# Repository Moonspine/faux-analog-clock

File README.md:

# Faux Analog Clock

An analog clock composed entirely of LEDs

The build should be fairly self-explanatory. A KiCad 6 schematic and board layout are included in `Board\`  
Additionally, `Board\Faux Analog Clock Gerber.zip` is a ready-to-go Gerber plot of the board which can be sent directly to the PCB manufacturer of your choice.  
LED resistor values are mere suggestions, and you should experiment on a breadboard to see what works well with your chosen LEDs.  

The following photos show the clock operating with its "Fill 2" (F2) display mode active:  

# Debugging the build

In order to facilitate easier debugging during the build process, two LED tests are easily accessible on startup.  

If you press and hold "Select" as you turn the clock on, it will boot in "LED test 1" mode.  
This mode displays all LEDs at full brightness to help track down bad solder joints, backwards diodes, etc.  
This test mode is accessible via the utilities menu after startup. Press any key to resume the normal boot sequence.  

If you press and hold "Enter" as you turn the clock on, it will boot in "LED test 2" mode.  
This mode displays each LED in sequence. This is useful for tracking down solder bridges and confirming proper clock operation.  
This test mode is also accessible via the utilities menu after startup. Press any key to resume the normal boot sequence.  

# Using the menu

Press "Select" or "Enter" to enter the menu.  
Subsequent presses of "Select" will advance to different menu options.  
Pressing "Enter" will choose a menu option (either changing a setting or opening a submenu.)  
Pressing and holding "Select" for the amount of time defined by MENU_BACK_BUTTON_LONG_PRESS_MS will return to the previous menu (or close the menu if at the top menu.)  
If no buttons are pressed for MENU_TIMEOUT_MS milliseconds, the menu will close on its own.

## Main menu options
- tZ (72) = Timezone
- dS (d5) = Daylight Saving Time
- FE (FE) = Face effects (Clock face ring effects)
- Fd (Fd) = Fade effects
- br (br) = Brightness
- nb (nb) = Night brightness (multiplied by brightness)
- dY (d4) = Display mode
- Pd (Pd) = Pendulum period
- UT (U7) = Utilities

## Timezone menu

In this menu, you can select the timezone offset of the clock, in whole hour increments.  
These values are displayed in hexadecimal (sorry, 7-segment displays) ranging from "-C" (-12 hours) to "E" (+14 hours)

## Daylight Saving Time menu

In this menu, you can set whether DST is in effect ("Y") or not ("n")

## Face Effects menu

This menu controls the face edge lighting.
- "on" = Face effects are turned on (fading between inner and outer at sunrise/sunset)
- "ou" = Face effects are turned off, always light outer clock face ring
- "in" = Face effects are turned off, always light inner clock face ring
- "bo" = Face effects are turned off, always light both clock face rings

## Fade Effects menu

This menu turns the LED intensity fade effects on ("Y") or off ("n")

## Brightness menu

This menu controls overall clock LED brightness from 1 (dimmest) to 10 (brightest).

## Night Brightness menu

This menu controls overall clock LED brightness at night (from 6 PM to 6 AM) from 1 (dimmest) to 10 (brightest).  
This value is multiplied by the overall clock brightness, making it effectively a scalar for clock brightness that's only applied at night.

## Display mode menu

This menu allows you to select between different clock face display modes.
- "An" = Analog mode. This is the classic analog clock face, showing one LED for hours, one for minutes, and one for seconds.
- "bn" = Binary mode. This mode displays H/M/S in binary. The LSb is at 12 o'clock, and the bits are displayed in clockwise order from there. The hours use 3 LEDs per bit (displaying a 4-bit number in total), and the minutes and seconds each use 10 LEDs per bit (displaying a 6-bit number).
- "F1" = Fill mode 1. This mode fills the hour/minute/second rings as time progresses, clearing them at the turn of the minute/hour.
- "F2" = Fill mode 2. This mode fills the hour/minute/second rings on even minutes/hours/AM (respectively), and empties the rings on odd mintes/hours/PM.
- "In" = Inverted analog mode. This is the same as analog move, except that the LEDs are inverted.

## Pendulum period menu

This menu allows you to set the period of the pendulum.
- "FA" = Fast (1 second)
- "SL" = Slow (2 seconds)

## Utilities menu

This menu includes some useful utilities for testing your clock build.
- "RS" ("r5") = Reset the current time using the GPS
- "L1"        = Run LED test 1 (light all LEDs at max intensity) (press any button to end)
- "L2"        = Run LED test 2 (light LEDs at max intensity sequentially) (press any button to end)

# Customizing the clock

## Faux_Analog_Clock.ino

At the top of `Firmware/Faux_Analog_Clock/Faux_Analog_Clock.ino`, you can find many constants defined which alter the behavior of the clock.

You can change the fade animation rate by modifying variables in the "Animation timing variables" section.
- CLOCK_ANIM_*_FADE_TIME = The number of microseconds between each time the LEDs fade by 1 unit of intensity (255 is the max LED intensity)

Menu behavior can be configured as well:
- MENU_TIMEOUT_MS                = The number of milliseconds until the menu auto-closes after the last button press.
- MENU_BACK_BUTTON_LONG_PRESS_MS = The number of milliseconds the user must hold the "Select" button to return to the previous menu.

You can also change how often the GPS is used to set the RTC:
- TIMEKEEPER_GPS_TIME_SET_INTERVAL_SECONDS = Seconds in between time resets.

## ClockFace.h

FACE_INNER_HOURLY_BRIGHTNESS and FACE_OUTER_HOURLY_BRIGHTNESS define the brightness of the inner and outer edge rings on a per-hour basis.  
The first entry in each array is the brightness at midnight (hour 0), and the rest of the entries count up from there (1 AM, 2 AM, etc.)

## Pendulum.h
PENDULUM_LED_INDEX contains the LED indices of the pendulum for each individual millisecond following a second tick.  
The default pattern is a sinusoidal pendulum pattern that starts in the center and swings right then left.

## Timekeeper.h

In `Firmware/Faux_Analog_Clock/Timekeeper.h`, commenting out the following line will cause the timekeeper to use an internal millis()-based RTC rather than external RTC hardware:
```
#define USE_HARDWARE_RTC 1
```

You can also modify the amount of time that the timekeeper will attempt to get a fix before forcibly resetting the GPS (the default is 15 minutes):
```
#define GPS_RESET_TIMEOUT_MS 900000
```

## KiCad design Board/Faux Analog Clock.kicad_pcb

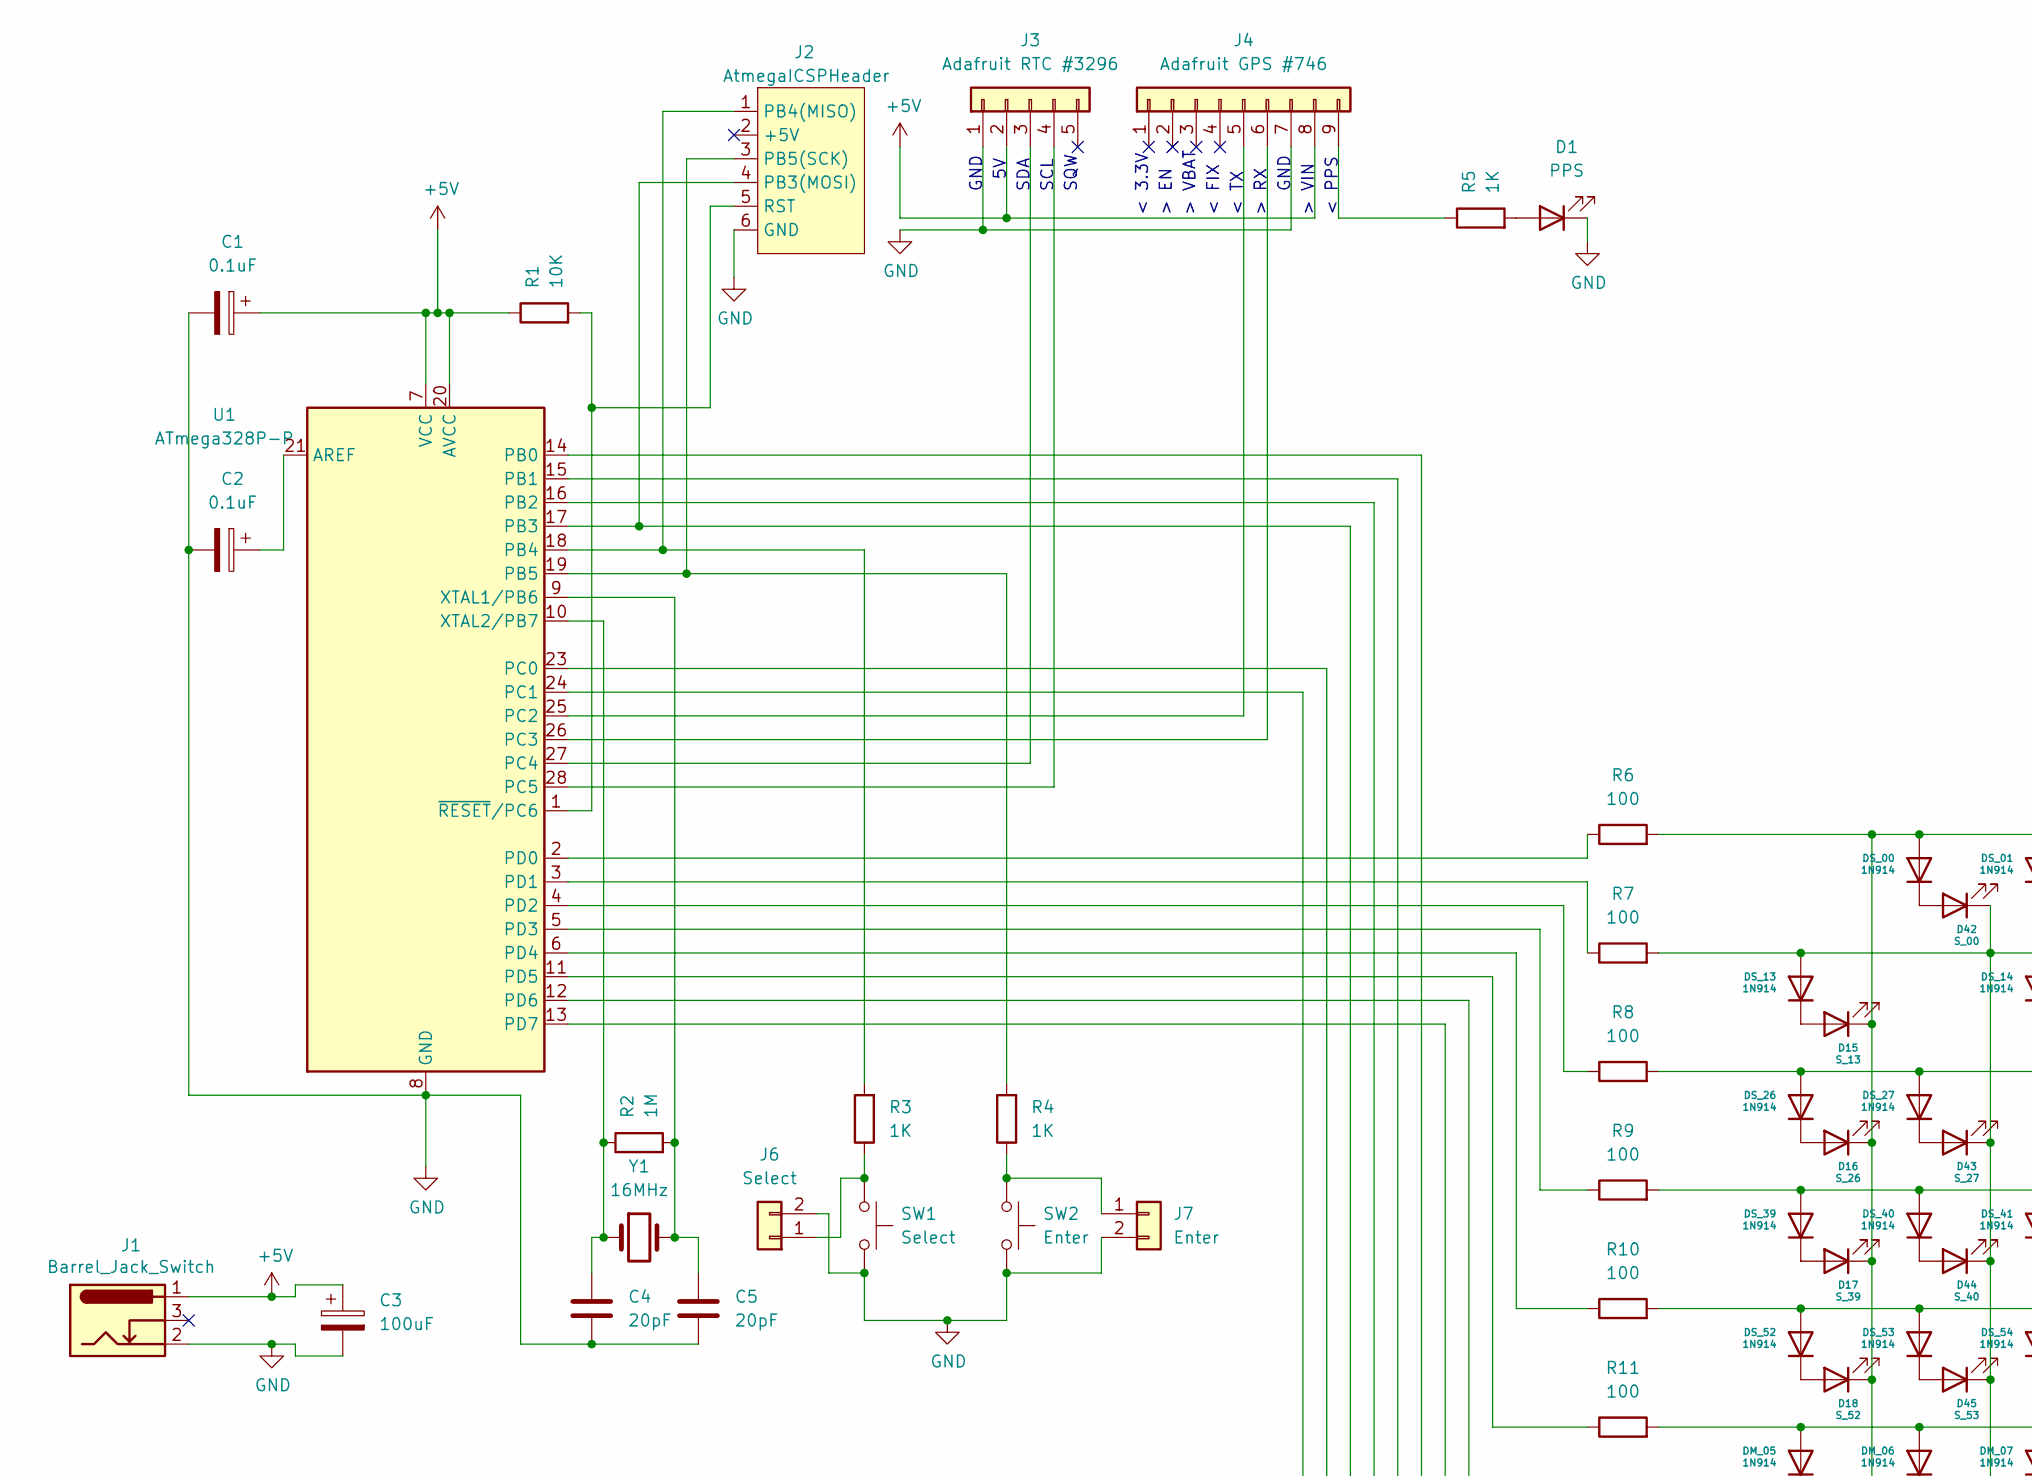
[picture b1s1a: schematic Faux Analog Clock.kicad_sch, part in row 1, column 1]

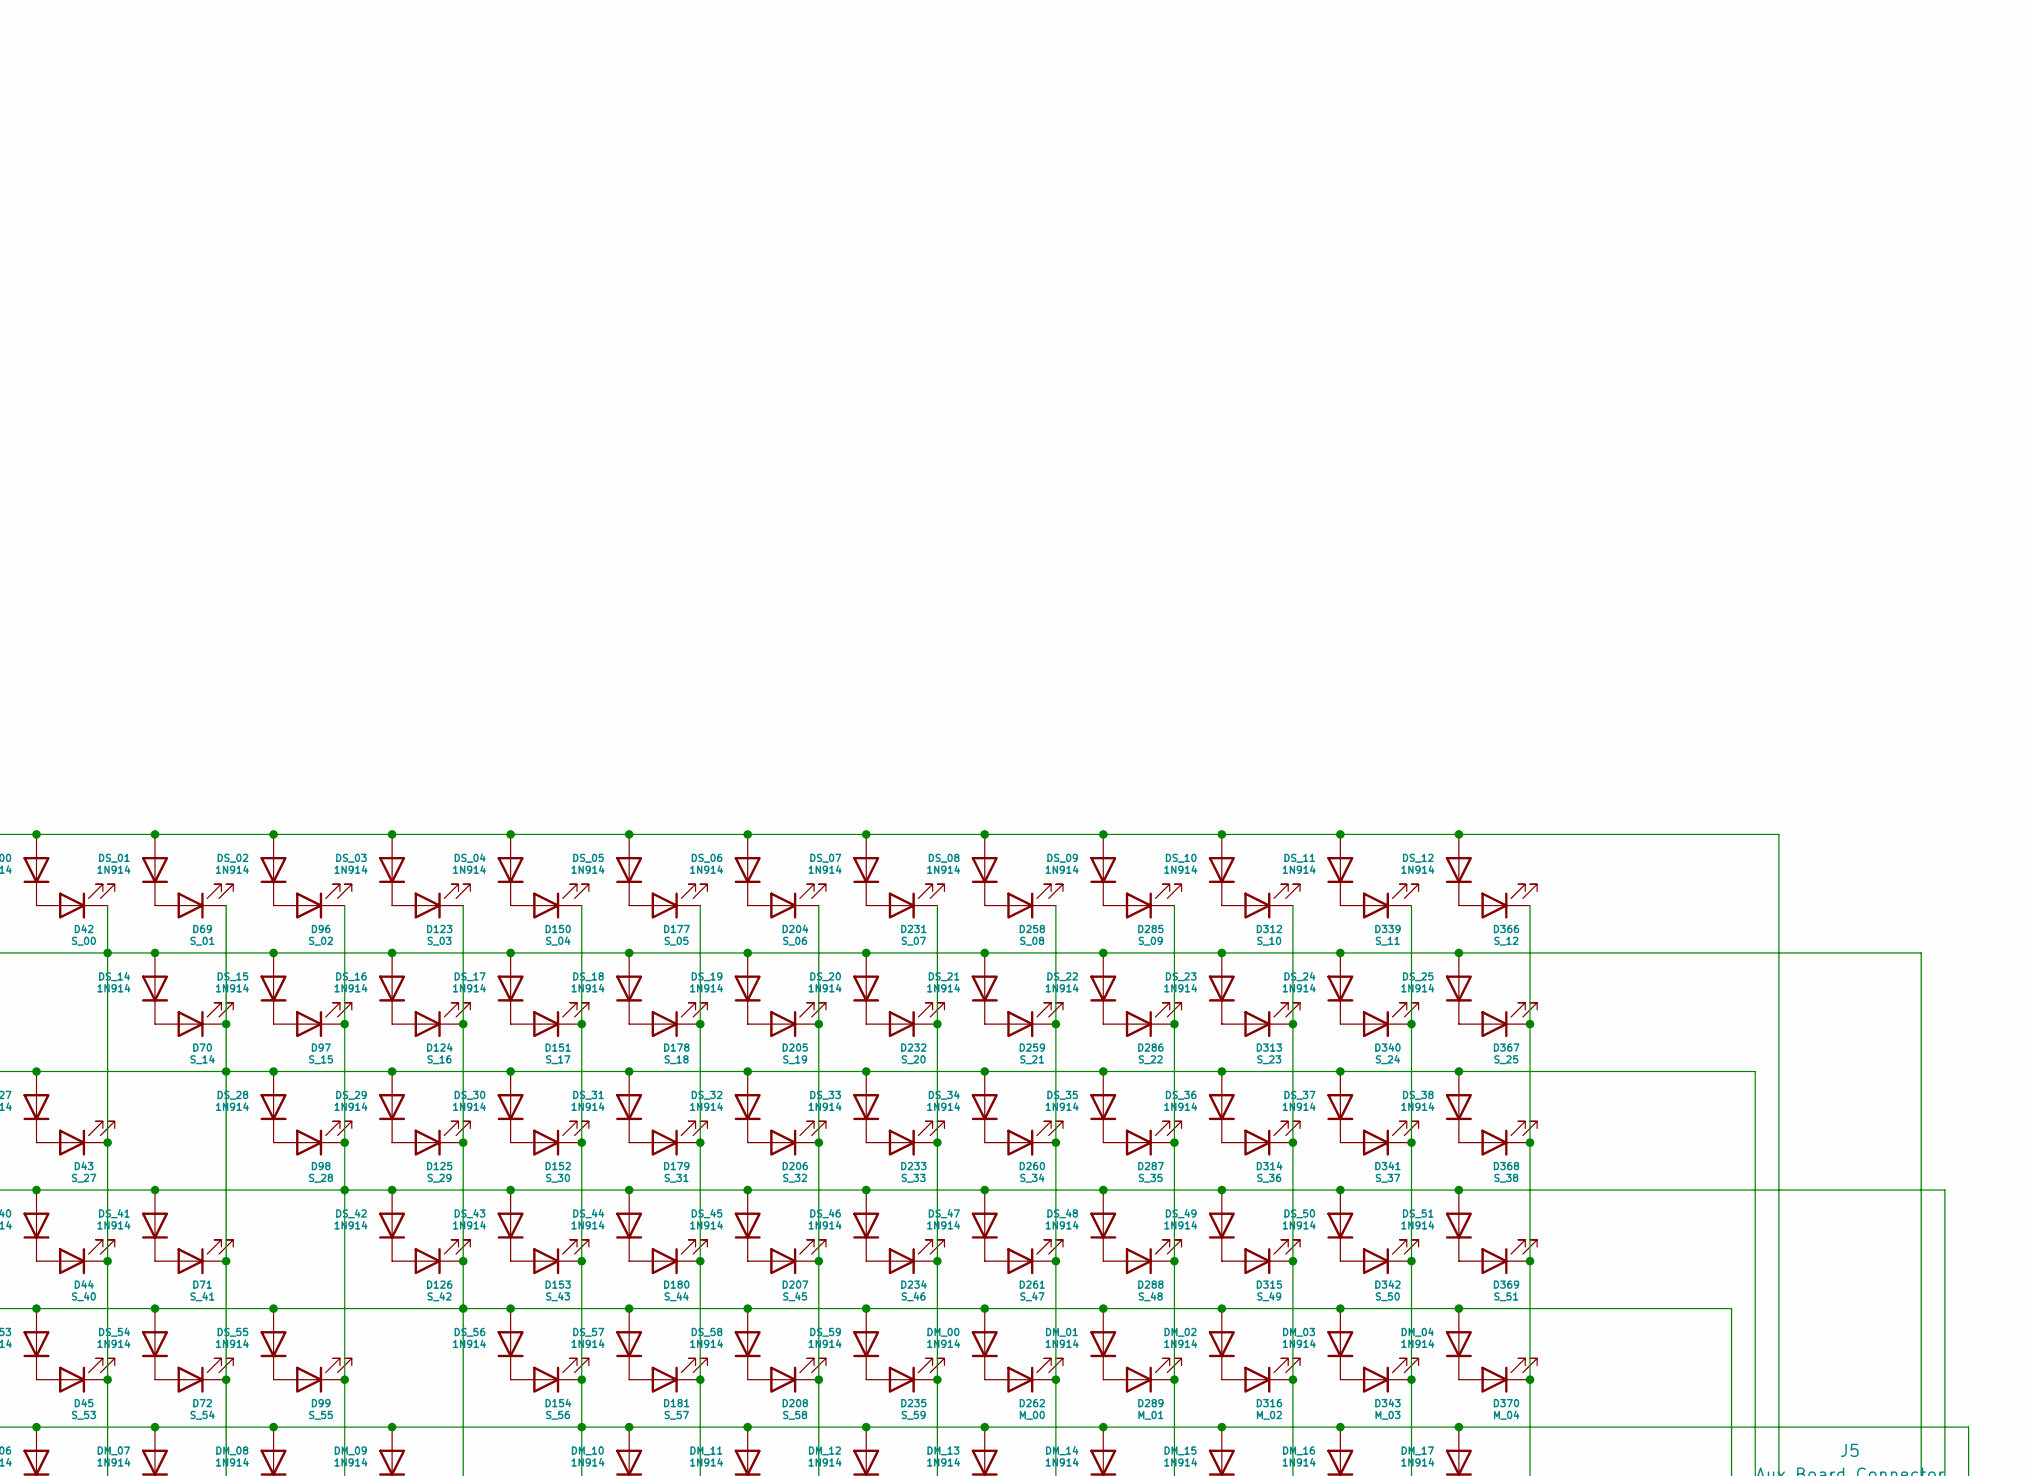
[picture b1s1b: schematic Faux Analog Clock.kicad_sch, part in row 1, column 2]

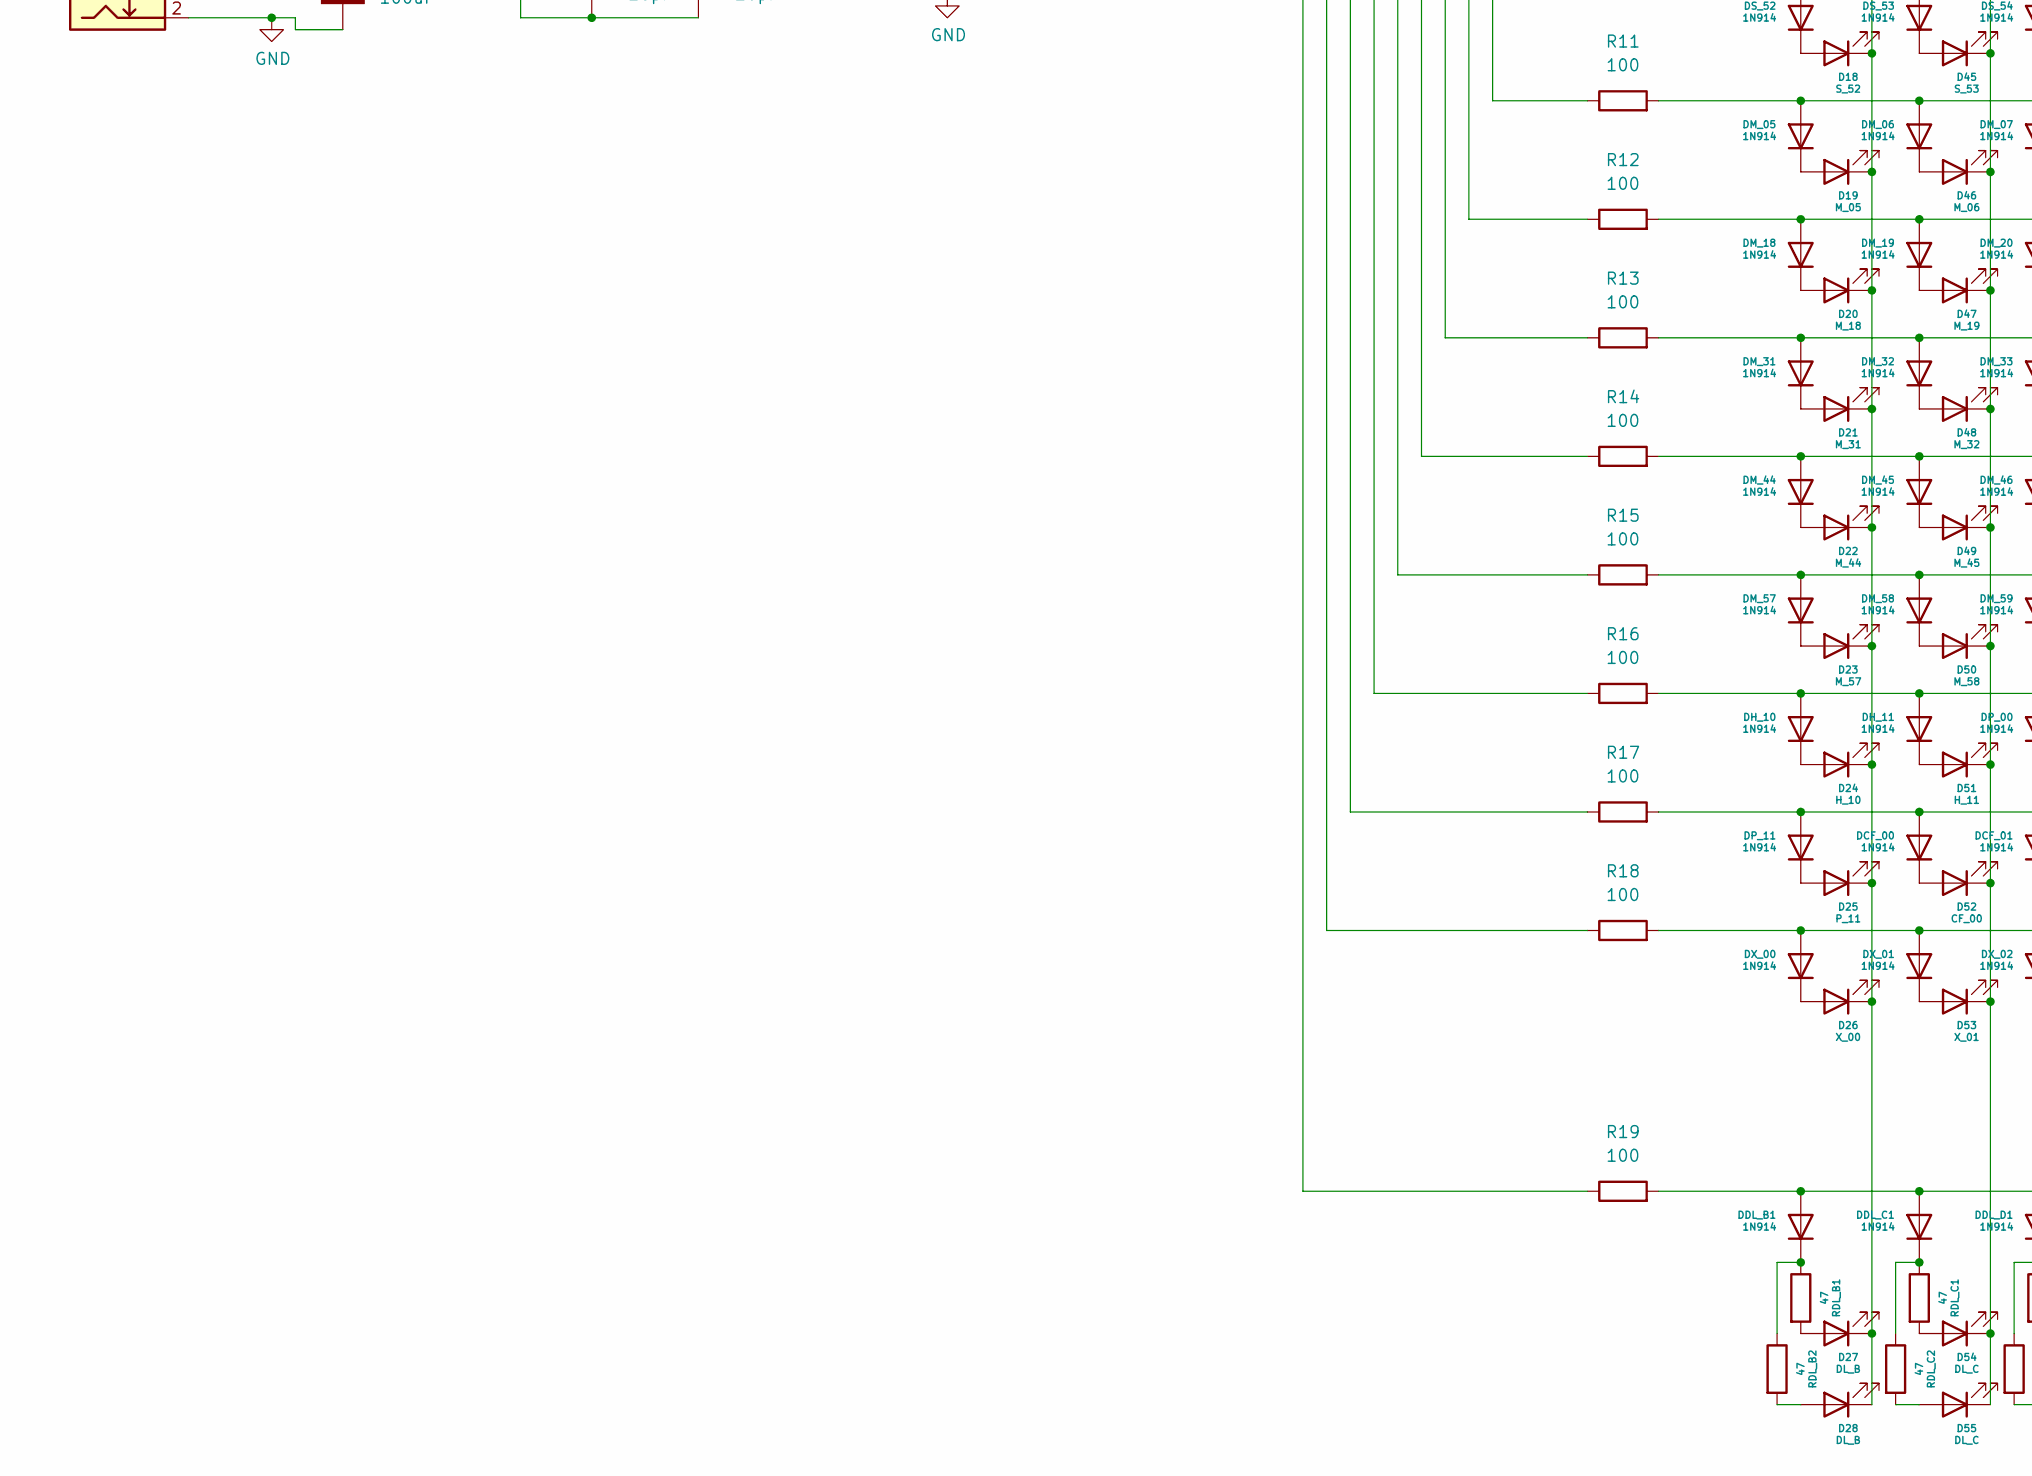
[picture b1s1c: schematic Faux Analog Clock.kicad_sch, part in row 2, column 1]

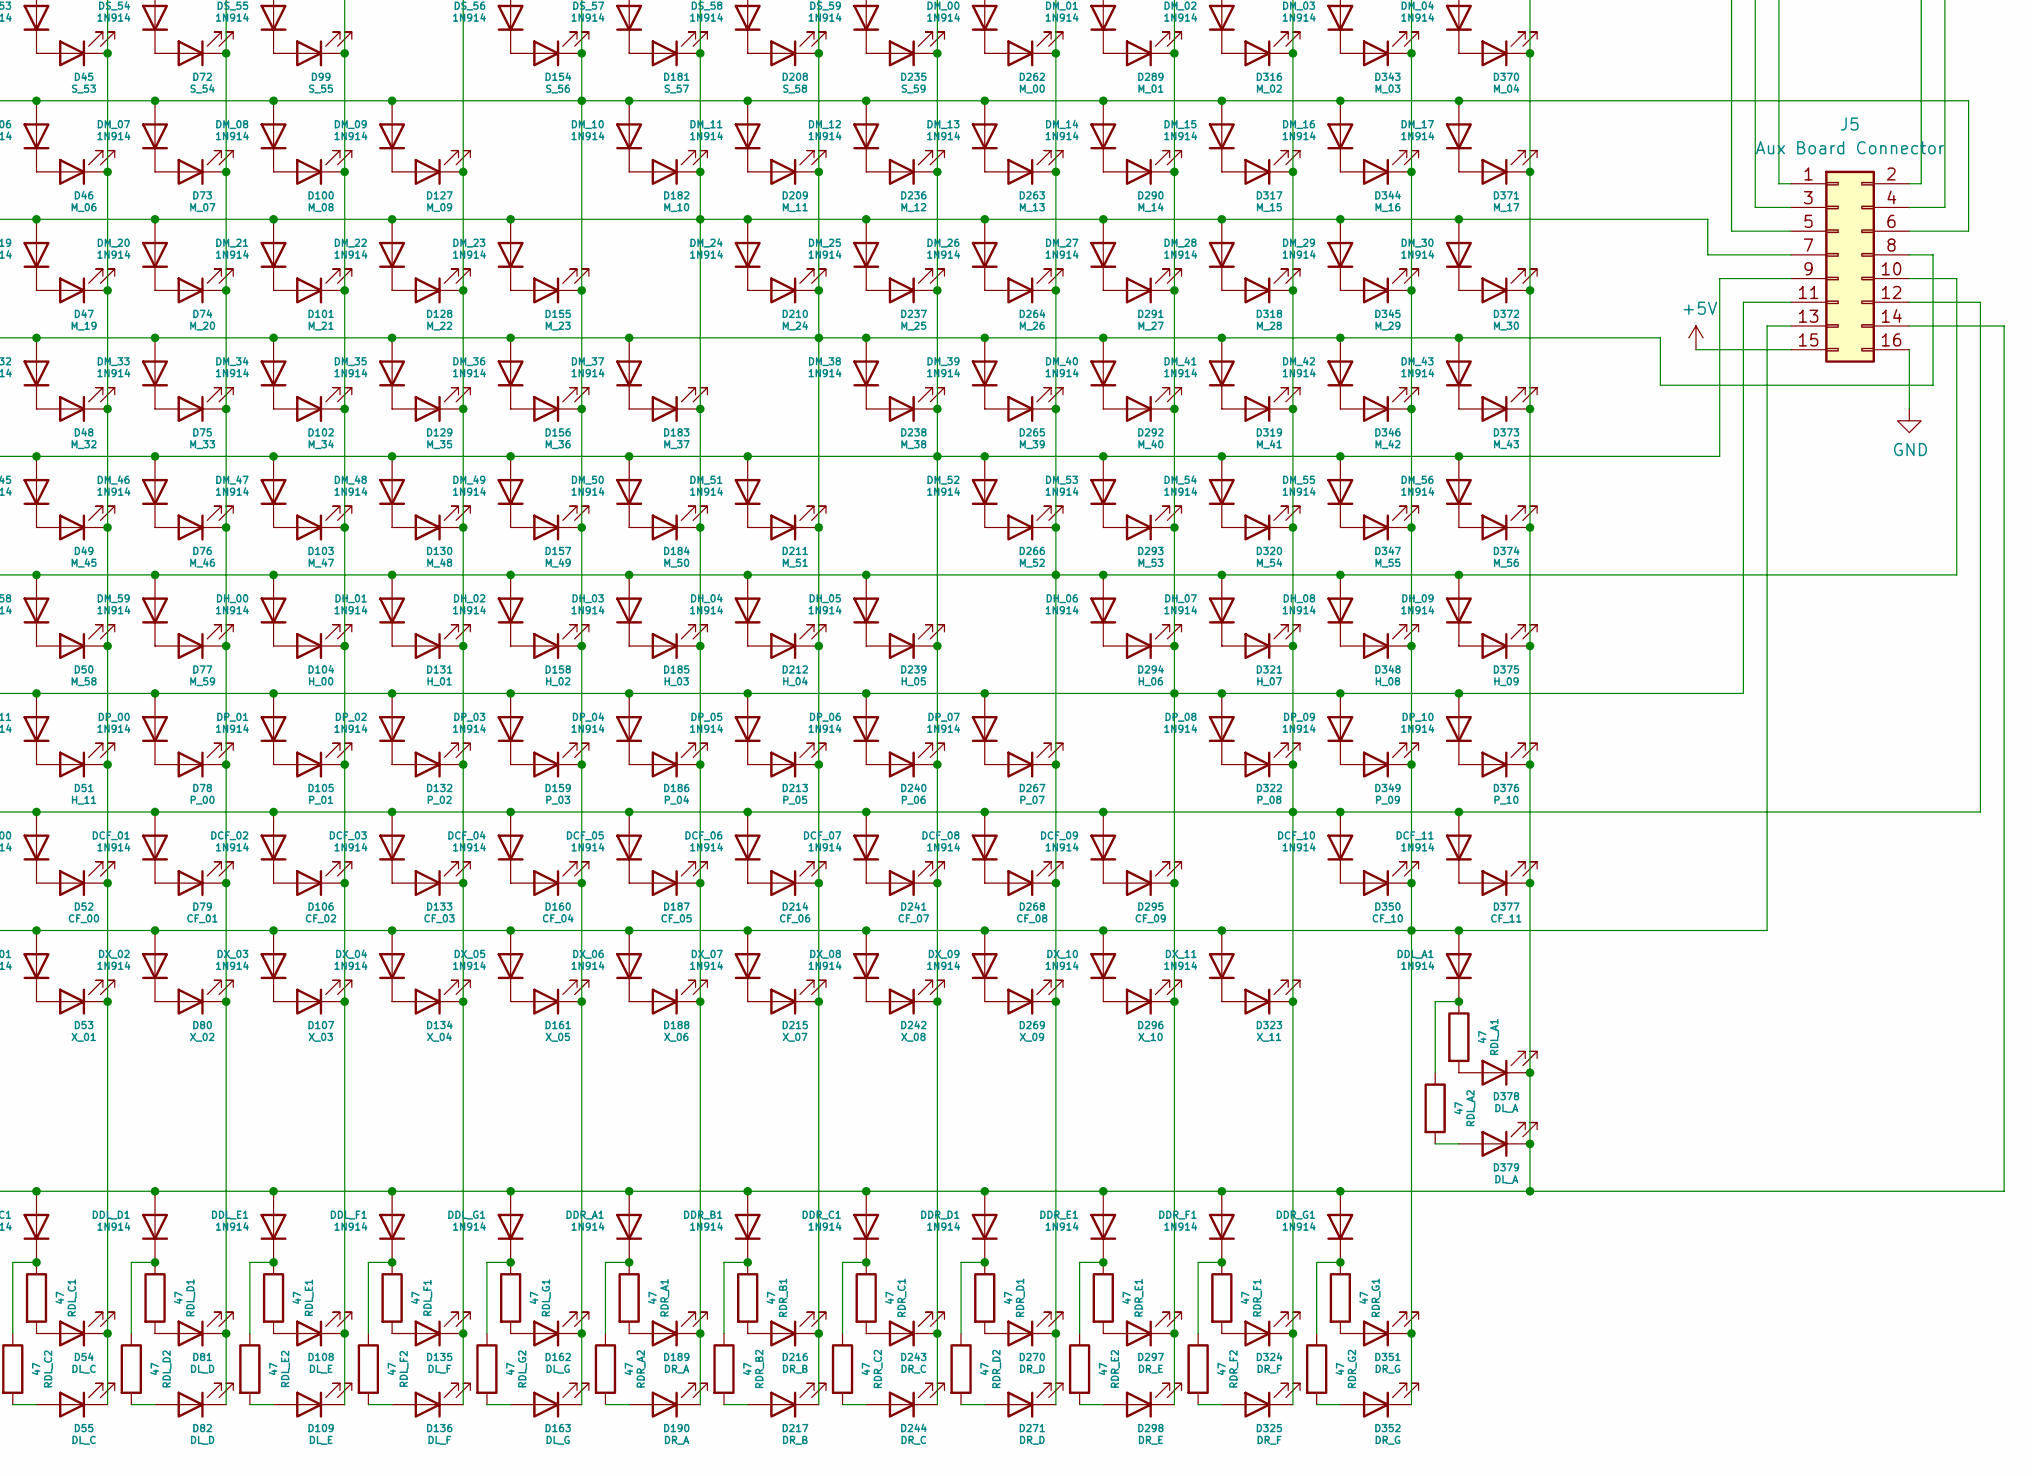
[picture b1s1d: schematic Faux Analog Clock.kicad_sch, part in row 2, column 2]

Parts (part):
C1, C2: 0.1uF; CP_Radial_Tantal_D5.0mm_P2.50mm
C3: 100uF; CP_Radial_D10.0mm_P3.50mm
C4, C5: 20pF; C_Disc_D5.0mm_W2.5mm_P2.50mm
D1: PPS; LED_D5.0mm
D15: S_13; LED_D5.0mm
D16: S_26; LED_D5.0mm
D17: S_39; LED_D5.0mm
D18: S_52; LED_D5.0mm
D19: M_05; LED_D5.0mm
D20: M_18; LED_D5.0mm
D21: M_31; LED_D5.0mm
D22: M_44; LED_D5.0mm
D23: M_57; LED_D5.0mm
D24: H_10; LED_D5.0mm
D25: P_11; LED_D5.0mm
D26: X_00; LED_D5.0mm
D27, D28: DL_B; LED_D5.0mm
D42: S_00; LED_D5.0mm
D43: S_27; LED_D5.0mm
D44: S_40; LED_D5.0mm
D45: S_53; LED_D5.0mm
D46: M_06; LED_D5.0mm
D47: M_19; LED_D5.0mm
D48: M_32; LED_D5.0mm
D49: M_45; LED_D5.0mm
D50: M_58; LED_D5.0mm
D51: H_11; LED_D5.0mm
D52: CF_00; LED_D5.0mm
D53: X_01; LED_D5.0mm
D54, D55: DL_C; LED_D5.0mm
D69: S_01; LED_D5.0mm
D70: S_14; LED_D5.0mm
D71: S_41; LED_D5.0mm
D72: S_54; LED_D5.0mm
D73: M_07; LED_D5.0mm
D74: M_20; LED_D5.0mm
D75: M_33; LED_D5.0mm
D76: M_46; LED_D5.0mm
D77: M_59; LED_D5.0mm
D78: P_00; LED_D5.0mm
D79: CF_01; LED_D5.0mm
D80: X_02; LED_D5.0mm
D81, D82: DL_D; LED_D5.0mm
D96: S_02; LED_D5.0mm
D97: S_15; LED_D5.0mm
D98: S_28; LED_D5.0mm
D99: S_55; LED_D5.0mm
D100: M_08; LED_D5.0mm
D101: M_21; LED_D5.0mm
D102: M_34; LED_D5.0mm
D103: M_47; LED_D5.0mm
D104: H_00; LED_D5.0mm
D105: P_01; LED_D5.0mm
D106: CF_02; LED_D5.0mm
D107: X_03; LED_D5.0mm
D108, D109: DL_E; LED_D5.0mm
D123: S_03; LED_D5.0mm
D124: S_16; LED_D5.0mm
D125: S_29; LED_D5.0mm
D126: S_42; LED_D5.0mm
D127: M_09; LED_D5.0mm
D128: M_22; LED_D5.0mm
D129: M_35; LED_D5.0mm
D130: M_48; LED_D5.0mm
D131: H_01; LED_D5.0mm
D132: P_02; LED_D5.0mm
D133: CF_03; LED_D5.0mm
D134: X_04; LED_D5.0mm
D135, D136: DL_F; LED_D5.0mm
D150: S_04; LED_D5.0mm
D151: S_17; LED_D5.0mm
D152: S_30; LED_D5.0mm
D153: S_43; LED_D5.0mm
D154: S_56; LED_D5.0mm
D155: M_23; LED_D5.0mm
D156: M_36; LED_D5.0mm
D157: M_49; LED_D5.0mm
D158: H_02; LED_D5.0mm
D159: P_03; LED_D5.0mm
D160: CF_04; LED_D5.0mm
D161: X_05; LED_D5.0mm
D162, D163: DL_G; LED_D5.0mm
D177: S_05; LED_D5.0mm
D178: S_18; LED_D5.0mm
D179: S_31; LED_D5.0mm
D180: S_44; LED_D5.0mm
D181: S_57; LED_D5.0mm
D182: M_10; LED_D5.0mm
D183: M_37; LED_D5.0mm
D184: M_50; LED_D5.0mm
D185: H_03; LED_D5.0mm
D186: P_04; LED_D5.0mm
D187: CF_05; LED_D5.0mm
D188: X_06; LED_D5.0mm
D189, D190: DR_A; LED_D5.0mm
D204: S_06; LED_D5.0mm
D205: S_19; LED_D5.0mm
D206: S_32; LED_D5.0mm
D207: S_45; LED_D5.0mm
D208: S_58; LED_D5.0mm
D209: M_11; LED_D5.0mm
D210: M_24; LED_D5.0mm
D211: M_51; LED_D5.0mm
D212: H_04; LED_D5.0mm
D213: P_05; LED_D5.0mm
D214: CF_06; LED_D5.0mm
D215: X_07; LED_D5.0mm
D216, D217: DR_B; LED_D5.0mm
D231: S_07; LED_D5.0mm
D232: S_20; LED_D5.0mm
D233: S_33; LED_D5.0mm
D234: S_46; LED_D5.0mm
D235: S_59; LED_D5.0mm
D236: M_12; LED_D5.0mm
D237: M_25; LED_D5.0mm
D238: M_38; LED_D5.0mm
D239: H_05; LED_D5.0mm
D240: P_06; LED_D5.0mm
D241: CF_07; LED_D5.0mm
D242: X_08; LED_D5.0mm
D243, D244: DR_C; LED_D5.0mm
D258: S_08; LED_D5.0mm
D259: S_21; LED_D5.0mm
D260: S_34; LED_D5.0mm
D261: S_47; LED_D5.0mm
D262: M_00; LED_D5.0mm
D263: M_13; LED_D5.0mm
D264: M_26; LED_D5.0mm
D265: M_39; LED_D5.0mm
D266: M_52; LED_D5.0mm
D267: P_07; LED_D5.0mm
D268: CF_08; LED_D5.0mm
D269: X_09; LED_D5.0mm
D270, D271: DR_D; LED_D5.0mm
D285: S_09; LED_D5.0mm
D286: S_22; LED_D5.0mm
D287: S_35; LED_D5.0mm
D288: S_48; LED_D5.0mm
D289: M_01; LED_D5.0mm
D290: M_14; LED_D5.0mm
D291: M_27; LED_D5.0mm
D292: M_40; LED_D5.0mm
D293: M_53; LED_D5.0mm
D294: H_06; LED_D5.0mm
D295: CF_09; LED_D5.0mm
D296: X_10; LED_D5.0mm
D297, D298: DR_E; LED_D5.0mm
D312: S_10; LED_D5.0mm
D313: S_23; LED_D5.0mm
D314: S_36; LED_D5.0mm
D315: S_49; LED_D5.0mm
D316: M_02; LED_D5.0mm
D317: M_15; LED_D5.0mm
D318: M_28; LED_D5.0mm
D319: M_41; LED_D5.0mm
D320: M_54; LED_D5.0mm
D321: H_07; LED_D5.0mm
D322: P_08; LED_D5.0mm
D323: X_11; LED_D5.0mm
D324, D325: DR_F; LED_D5.0mm
D339: S_11; LED_D5.0mm
D340: S_24; LED_D5.0mm
D341: S_37; LED_D5.0mm
D342: S_50; LED_D5.0mm
D343: M_03; LED_D5.0mm
D344: M_16; LED_D5.0mm
D345: M_29; LED_D5.0mm
D346: M_42; LED_D5.0mm
D347: M_55; LED_D5.0mm
D348: H_08; LED_D5.0mm
D349: P_09; LED_D5.0mm
D350: CF_10; LED_D5.0mm
D351, D352: DR_G; LED_D5.0mm
D366: S_12; LED_D5.0mm
D367: S_25; LED_D5.0mm
D368: S_38; LED_D5.0mm
D369: S_51; LED_D5.0mm
D370: M_04; LED_D5.0mm
D371: M_17; LED_D5.0mm
D372: M_30; LED_D5.0mm
D373: M_43; LED_D5.0mm
D374: M_56; LED_D5.0mm
D375: H_09; LED_D5.0mm
D376: P_10; LED_D5.0mm
D377: CF_11; LED_D5.0mm
D378, D379: DL_A; LED_D5.0mm
DCF_00, DCF_01, DCF_02, DCF_03, DCF_04, DCF_05, DCF_06, DCF_07, DCF_08, DCF_09, DCF_10, DCF_11: 1N914; D_DO-34_SOD68_P10.16mm_Horizontal
DDL_A1: 1N914; D_DO-34_SOD68_P10.16mm_Horizontal
DDL_B1: 1N914; D_DO-34_SOD68_P10.16mm_Horizontal
DDL_C1: 1N914; D_DO-34_SOD68_P10.16mm_Horizontal
DDL_D1: 1N914; D_DO-34_SOD68_P10.16mm_Horizontal
DDL_E1: 1N914; D_DO-34_SOD68_P10.16mm_Horizontal
DDL_F1: 1N914; D_DO-34_SOD68_P10.16mm_Horizontal
DDL_G1: 1N914; D_DO-34_SOD68_P10.16mm_Horizontal
DDR_A1: 1N914; D_DO-34_SOD68_P10.16mm_Horizontal
DDR_B1: 1N914; D_DO-34_SOD68_P10.16mm_Horizontal
DDR_C1: 1N914; D_DO-34_SOD68_P10.16mm_Horizontal
DDR_D1: 1N914; D_DO-34_SOD68_P10.16mm_Horizontal
DDR_E1: 1N914; D_DO-34_SOD68_P10.16mm_Horizontal
DDR_F1: 1N914; D_DO-34_SOD68_P10.16mm_Horizontal
DDR_G1: 1N914; D_DO-34_SOD68_P10.16mm_Horizontal
DH_00, DH_01, DH_02, DH_03, DH_04, DH_05, DH_06, DH_07, DH_08, DH_09, DH_10, DH_11: 1N914; D_DO-34_SOD68_P10.16mm_Horizontal
DM_00, DM_01, DM_02, DM_03, DM_04, DM_05, DM_06, DM_07, DM_08, DM_09, DM_10, DM_11, DM_12, DM_13, DM_14, DM_15, DM_16, DM_17, DM_18, DM_19, DM_20, DM_21, DM_22, DM_23, DM_24, DM_25, DM_26, DM_27, DM_28, DM_29, DM_30, DM_31, DM_32, DM_33, DM_34, DM_35, DM_36, DM_37, DM_38, DM_39, DM_40, DM_41, DM_42, DM_43, DM_44, DM_45, DM_46, DM_47, DM_48, DM_49, DM_50, DM_51, DM_52, DM_53, DM_54, DM_55, DM_56, DM_57, DM_58, DM_59: 1N914; D_DO-34_SOD68_P10.16mm_Horizontal
DP_00, DP_01, DP_02, DP_03, DP_04, DP_05, DP_06, DP_07, DP_08, DP_09, DP_10, DP_11: 1N914; D_DO-34_SOD68_P10.16mm_Horizontal
DS_00, DS_01, DS_02, DS_03, DS_04, DS_05, DS_06, DS_07, DS_08, DS_09, DS_10, DS_11, DS_12, DS_13, DS_14, DS_15, DS_16, DS_17, DS_18, DS_19, DS_20, DS_21, DS_22, DS_23, DS_24, DS_25, DS_26, DS_27, DS_28, DS_29, DS_30, DS_31, DS_32, DS_33, DS_34, DS_35, DS_36, DS_37, DS_38, DS_39, DS_40, DS_41, DS_42, DS_43, DS_44, DS_45, DS_46, DS_47, DS_48, DS_49, DS_50, DS_51, DS_52, DS_53, DS_54, DS_55, DS_56, DS_57, DS_58, DS_59: 1N914; D_DO-34_SOD68_P10.16mm_Horizontal
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
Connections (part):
+5V: C1.1, C3.1, J1.1, J3.2, J4.8, J5.15, R1.1, U1.7 (VCC), U1.20 (AVCC)
GND: C1.2, C2.2, C3.2, C4.2, C5.2, D1.1 (K), J1.2, J2.6 (GND), J3.1, J4.7, J5.16, J6.2, J7.2, SW1.2, SW2.2, U1.8 (GND), U1.22 (GND)
unnamed: C2.1, U1.21 (AREF)
unnamed: C4.1, R2.1, U1.10 (XTAL2/PB7), Y1.1
unnamed: C5.1, R2.2, U1.9 (XTAL1/PB6), Y1.2
unnamed: D1.2 (A), R5.2
unnamed: D15.1 (K), D16.1 (K), D17.1 (K), D18.1 (K), D19.1 (K), D20.1 (K), D21.1 (K), D22.1 (K), D23.1 (K), D24.1 (K), D25.1 (K), D26.1 (K), D27.1 (K), D28.1 (K), DS_00.2 (A), DS_01.2 (A), DS_02.2 (A), DS_03.2 (A), DS_04.2 (A), DS_05.2 (A), DS_06.2 (A), DS_07.2 (A), DS_08.2 (A), DS_09.2 (A), DS_10.2 (A), DS_11.2 (A), DS_12.2 (A), J5.1, R6.2
unnamed: D15.2 (A), DS_13.1 (K)
unnamed: D16.2 (A), DS_26.1 (K)
unnamed: D17.2 (A), DS_39.1 (K)
unnamed: D18.2 (A), DS_52.1 (K)
unnamed: D19.2 (A), DM_05.1 (K)
unnamed: D20.2 (A), DM_18.1 (K)
unnamed: D21.2 (A), DM_31.1 (K)
unnamed: D22.2 (A), DM_44.1 (K)
unnamed: D23.2 (A), DM_57.1 (K)
unnamed: D24.2 (A), DH_10.1 (K)
unnamed: D25.2 (A), DP_11.1 (K)
unnamed: D26.2 (A), DX_00.1 (K)
unnamed: D27.2 (A), RDL_B1.2
unnamed: D28.2 (A), RDL_B2.2
unnamed: D42.1 (K), D43.1 (K), D44.1 (K), D45.1 (K), D46.1 (K), D47.1 (K), D48.1 (K), D49.1 (K), D50.1 (K), D51.1 (K), D52.1 (K), D53.1 (K), D54.1 (K), D55.1 (K), DS_13.2 (A), DS_14.2 (A), DS_15.2 (A), DS_16.2 (A), DS_17.2 (A), DS_18.2 (A), DS_19.2 (A), DS_20.2 (A), DS_21.2 (A), DS_22.2 (A), DS_23.2 (A), DS_24.2 (A), DS_25.2 (A), J5.2, R7.2
unnamed: D42.2 (A), DS_00.1 (K)
unnamed: D43.2 (A), DS_27.1 (K)
unnamed: D44.2 (A), DS_40.1 (K)
unnamed: D45.2 (A), DS_53.1 (K)
unnamed: D46.2 (A), DM_06.1 (K)
unnamed: D47.2 (A), DM_19.1 (K)
unnamed: D48.2 (A), DM_32.1 (K)
unnamed: D49.2 (A), DM_45.1 (K)
unnamed: D50.2 (A), DM_58.1 (K)
unnamed: D51.2 (A), DH_11.1 (K)
unnamed: D52.2 (A), DCF_00.1 (K)
unnamed: D53.2 (A), DX_01.1 (K)
unnamed: D54.2 (A), RDL_C1.2
unnamed: D55.2 (A), RDL_C2.2
unnamed: D69.1 (K), D70.1 (K), D71.1 (K), D72.1 (K), D73.1 (K), D74.1 (K), D75.1 (K), D76.1 (K), D77.1 (K), D78.1 (K), D79.1 (K), D80.1 (K), D81.1 (K), D82.1 (K), DS_26.2 (A), DS_27.2 (A), DS_28.2 (A), DS_29.2 (A), DS_30.2 (A), DS_31.2 (A), DS_32.2 (A), DS_33.2 (A), DS_34.2 (A), DS_35.2 (A), DS_36.2 (A), DS_37.2 (A), DS_38.2 (A), J5.3, R8.2
unnamed: D69.2 (A), DS_01.1 (K)
unnamed: D70.2 (A), DS_14.1 (K)
unnamed: D71.2 (A), DS_41.1 (K)
unnamed: D72.2 (A), DS_54.1 (K)
unnamed: D73.2 (A), DM_07.1 (K)
unnamed: D74.2 (A), DM_20.1 (K)
unnamed: D75.2 (A), DM_33.1 (K)
unnamed: D76.2 (A), DM_46.1 (K)
unnamed: D77.2 (A), DM_59.1 (K)
unnamed: D78.2 (A), DP_00.1 (K)
unnamed: D79.2 (A), DCF_01.1 (K)
unnamed: D80.2 (A), DX_02.1 (K)
unnamed: D81.2 (A), RDL_D1.2
unnamed: D82.2 (A), RDL_D2.2
unnamed: D96.2 (A), DS_02.1 (K)
unnamed: D97.2 (A), DS_15.1 (K)
unnamed: D98.2 (A), DS_28.1 (K)
unnamed: D99.2 (A), DS_55.1 (K)
unnamed: D96.1 (K), D97.1 (K), D98.1 (K), D99.1 (K), D100.1 (K), D101.1 (K), D102.1 (K), D103.1 (K), D104.1 (K), D105.1 (K), D106.1 (K), D107.1 (K), D108.1 (K), D109.1 (K), DS_39.2 (A), DS_40.2 (A), DS_41.2 (A), DS_42.2 (A), DS_43.2 (A), DS_44.2 (A), DS_45.2 (A), DS_46.2 (A), DS_47.2 (A), DS_48.2 (A), DS_49.2 (A), DS_50.2 (A), DS_51.2 (A), J5.4, R9.2
unnamed: D100.2 (A), DM_08.1 (K)
unnamed: D101.2 (A), DM_21.1 (K)
unnamed: D102.2 (A), DM_34.1 (K)
unnamed: D103.2 (A), DM_47.1 (K)
unnamed: D104.2 (A), DH_00.1 (K)
unnamed: D105.2 (A), DP_01.1 (K)
unnamed: D106.2 (A), DCF_02.1 (K)
unnamed: D107.2 (A), DX_03.1 (K)
unnamed: D108.2 (A), RDL_E1.2
unnamed: D109.2 (A), RDL_E2.2
unnamed: D123.1 (K), D124.1 (K), D125.1 (K), D126.1 (K), D127.1 (K), D128.1 (K), D129.1 (K), D130.1 (K), D131.1 (K), D132.1 (K), D133.1 (K), D134.1 (K), D135.1 (K), D136.1 (K), DM_00.2 (A), DM_01.2 (A), DM_02.2 (A), DM_03.2 (A), DM_04.2 (A), DS_52.2 (A), DS_53.2 (A), DS_54.2 (A), DS_55.2 (A), DS_56.2 (A), DS_57.2 (A), DS_58.2 (A), DS_59.2 (A), J5.5, R10.2
unnamed: D123.2 (A), DS_03.1 (K)
unnamed: D124.2 (A), DS_16.1 (K)
unnamed: D125.2 (A), DS_29.1 (K)
unnamed: D126.2 (A), DS_42.1 (K)
unnamed: D127.2 (A), DM_09.1 (K)
unnamed: D128.2 (A), DM_22.1 (K)
unnamed: D129.2 (A), DM_35.1 (K)
unnamed: D130.2 (A), DM_48.1 (K)
unnamed: D131.2 (A), DH_01.1 (K)
unnamed: D132.2 (A), DP_02.1 (K)
unnamed: D133.2 (A), DCF_03.1 (K)
unnamed: D134.2 (A), DX_04.1 (K)
unnamed: D135.2 (A), RDL_F1.2
unnamed: D136.2 (A), RDL_F2.2
unnamed: D150.1 (K), D151.1 (K), D152.1 (K), D153.1 (K), D154.1 (K), D155.1 (K), D156.1 (K), D157.1 (K), D158.1 (K), D159.1 (K), D160.1 (K), D161.1 (K), D162.1 (K), D163.1 (K), DM_05.2 (A), DM_06.2 (A), DM_07.2 (A), DM_08.2 (A), DM_09.2 (A), DM_10.2 (A), DM_11.2 (A), DM_12.2 (A), DM_13.2 (A), DM_14.2 (A), DM_15.2 (A), DM_16.2 (A), DM_17.2 (A), J5.6, R11.2
unnamed: D150.2 (A), DS_04.1 (K)
unnamed: D151.2 (A), DS_17.1 (K)
unnamed: D152.2 (A), DS_30.1 (K)
unnamed: D153.2 (A), DS_43.1 (K)
unnamed: D154.2 (A), DS_56.1 (K)
unnamed: D155.2 (A), DM_23.1 (K)
unnamed: D156.2 (A), DM_36.1 (K)
unnamed: D157.2 (A), DM_49.1 (K)
unnamed: D158.2 (A), DH_02.1 (K)
unnamed: D159.2 (A), DP_03.1 (K)
unnamed: D160.2 (A), DCF_04.1 (K)
unnamed: D161.2 (A), DX_05.1 (K)
unnamed: D162.2 (A), RDL_G1.2
unnamed: D163.2 (A), RDL_G2.2
unnamed: D177.1 (K), D178.1 (K), D179.1 (K), D180.1 (K), D181.1 (K), D182.1 (K), D183.1 (K), D184.1 (K), D185.1 (K), D186.1 (K), D187.1 (K), D188.1 (K), D189.1 (K), D190.1 (K), DM_18.2 (A), DM_19.2 (A), DM_20.2 (A), DM_21.2 (A), DM_22.2 (A), DM_23.2 (A), DM_24.2 (A), DM_25.2 (A), DM_26.2 (A), DM_27.2 (A), DM_28.2 (A), DM_29.2 (A), DM_30.2 (A), J5.7, R12.2
unnamed: D177.2 (A), DS_05.1 (K)
unnamed: D178.2 (A), DS_18.1 (K)
unnamed: D179.2 (A), DS_31.1 (K)
unnamed: D180.2 (A), DS_44.1 (K)
unnamed: D181.2 (A), DS_57.1 (K)
unnamed: D182.2 (A), DM_10.1 (K)
unnamed: D183.2 (A), DM_37.1 (K)
unnamed: D184.2 (A), DM_50.1 (K)
unnamed: D185.2 (A), DH_03.1 (K)
unnamed: D186.2 (A), DP_04.1 (K)
unnamed: D187.2 (A), DCF_05.1 (K)
unnamed: D188.2 (A), DX_06.1 (K)
unnamed: D189.2 (A), RDR_A1.2
unnamed: D190.2 (A), RDR_A2.2
unnamed: D204.1 (K), D205.1 (K), D206.1 (K), D207.1 (K), D208.1 (K), D209.1 (K), D210.1 (K), D211.1 (K), D212.1 (K), D213.1 (K), D214.1 (K), D215.1 (K), D216.1 (K), D217.1 (K), DM_31.2 (A), DM_32.2 (A), DM_33.2 (A), DM_34.2 (A), DM_35.2 (A), DM_36.2 (A), DM_37.2 (A), DM_38.2 (A), DM_39.2 (A), DM_40.2 (A), DM_41.2 (A), DM_42.2 (A), DM_43.2 (A), J5.8, R13.2
unnamed: D204.2 (A), DS_06.1 (K)
unnamed: D205.2 (A), DS_19.1 (K)
unnamed: D206.2 (A), DS_32.1 (K)
unnamed: D207.2 (A), DS_45.1 (K)
unnamed: D208.2 (A), DS_58.1 (K)
unnamed: D209.2 (A), DM_11.1 (K)
unnamed: D210.2 (A), DM_24.1 (K)
unnamed: D211.2 (A), DM_51.1 (K)
unnamed: D212.2 (A), DH_04.1 (K)
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
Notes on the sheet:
> RX
GND
< FIX
SDA
< TX
> EN
SCL
SQW
< PPS
< 3.3V
> VBAT
> VIN

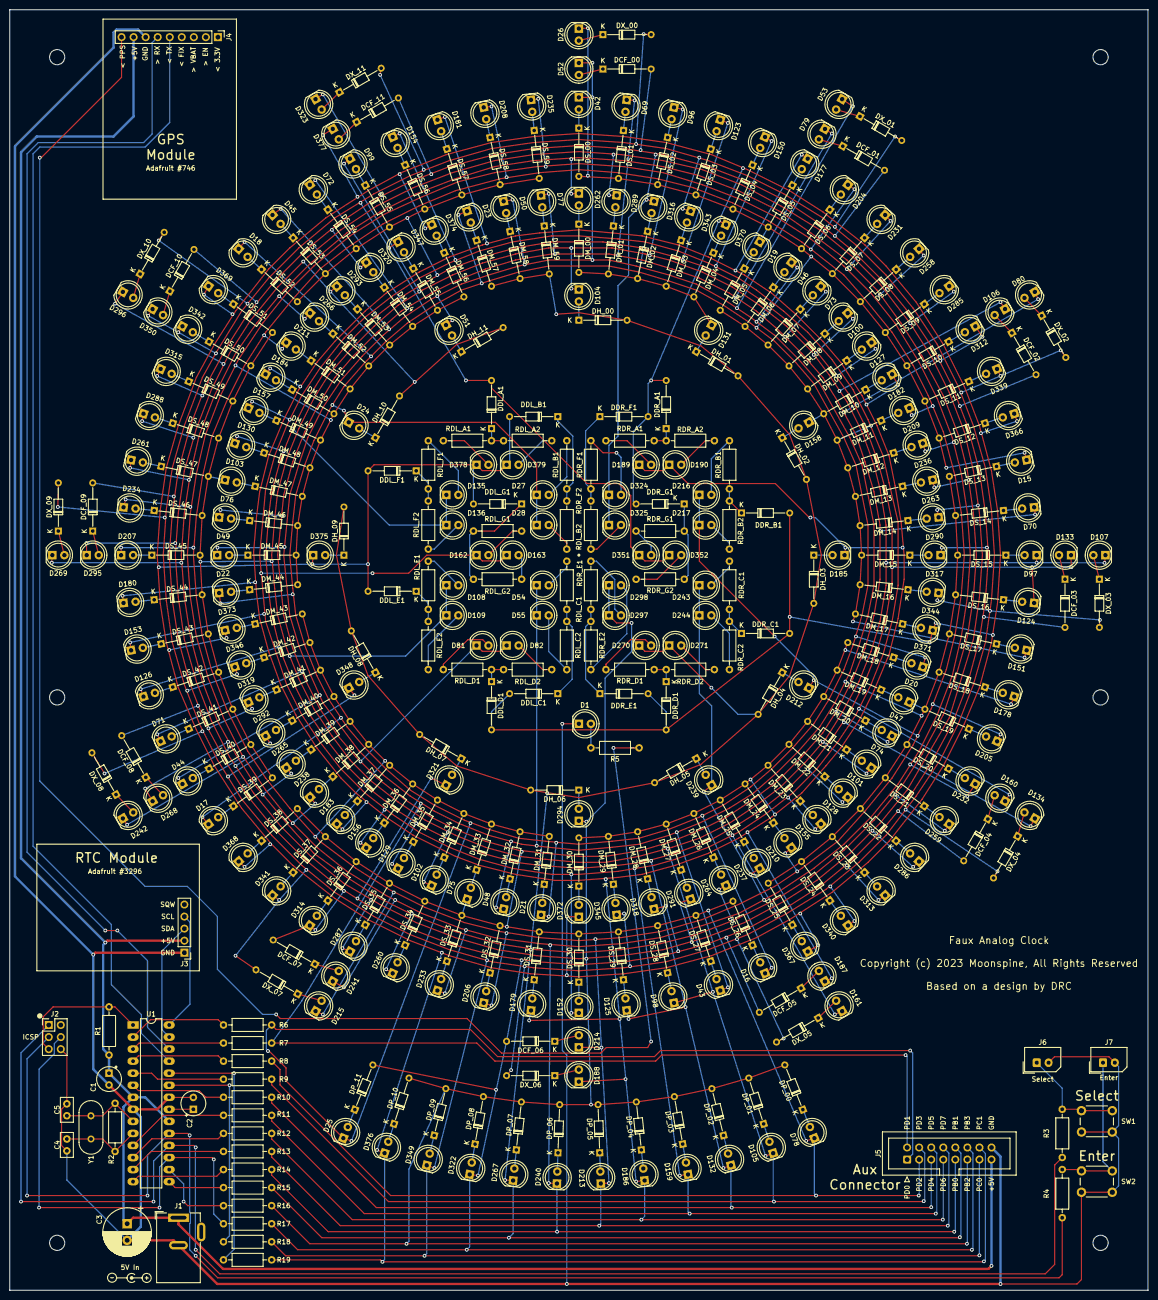
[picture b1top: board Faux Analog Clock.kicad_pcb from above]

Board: 2 copper layers, 240.0 x 270.0 mm, 442 parts (0 on the bottom side), 254 nets.

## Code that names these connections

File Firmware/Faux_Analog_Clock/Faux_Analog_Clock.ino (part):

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 *  Adafruit GPS 1.7.2
 * 
 * Pinout:
 *  RTC SDA            = PC4
 *  RTC SCL            = PC5
 *  GPS TX             = PC2
 *  GPS RX             = PC3
 *  Charlieplex 0..7   = PORTD 0..7
 *  Charlieplex 8..11  = PORTB 0..3
 *  Charlieplex 12..13 = PORTC 0..1
 *  Select Button      = PB4
 *  Enter Button       = PB5
 */

/*
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
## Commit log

2023-07-20 .gitignore
2023-07-20 Formatting
2023-07-20 Removed TODO
2023-07-20 Fixed issue with outer rings when setting time
2023-07-20 Fade effects now use microseconds; Added binary display mode
2023-07-23 Reduced ghosting
2023-07-24 Added fill 1, fill 2, inverted analog display modes
2023-07-24 Fixed clock ring snap bug
2023-07-25 Added quick debug features by holding Select or Enter on boot
2023-07-28 Time setting is more robust
2023-08-07 Resistor values tweaked
2023-08-15 Reset GPS if it doesn't achieve a fix within 15 minutes
2023-08-16 Fixed typos
2023-08-21 Added pendulum period menu option
2023-08-22 Added clock photos

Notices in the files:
Board/Faux Analog Clock.kicad_pcb:
Copyright (c) 2023 Moonspine, All Rights Reserved
